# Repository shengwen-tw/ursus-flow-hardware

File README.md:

#Ursus-flow

This is the hardware design of Ursus-flow, a computer vision board provide speed estimation for multi-rotor.

##Specification

**MCU**: STM32F745VETX

**Camera**: MT9v034 (I2C1 and DCMI)

**IMU**: MPU9250 (SPI1)

**Height sensor**: Lidar lite v2 (I2C2)

**USB**: Full Speed USB (USB2.0)

**EEPROM**: AT24C08 (I2C3)

UART2: Data output to flight control board

UART3 and SPI2: alternation

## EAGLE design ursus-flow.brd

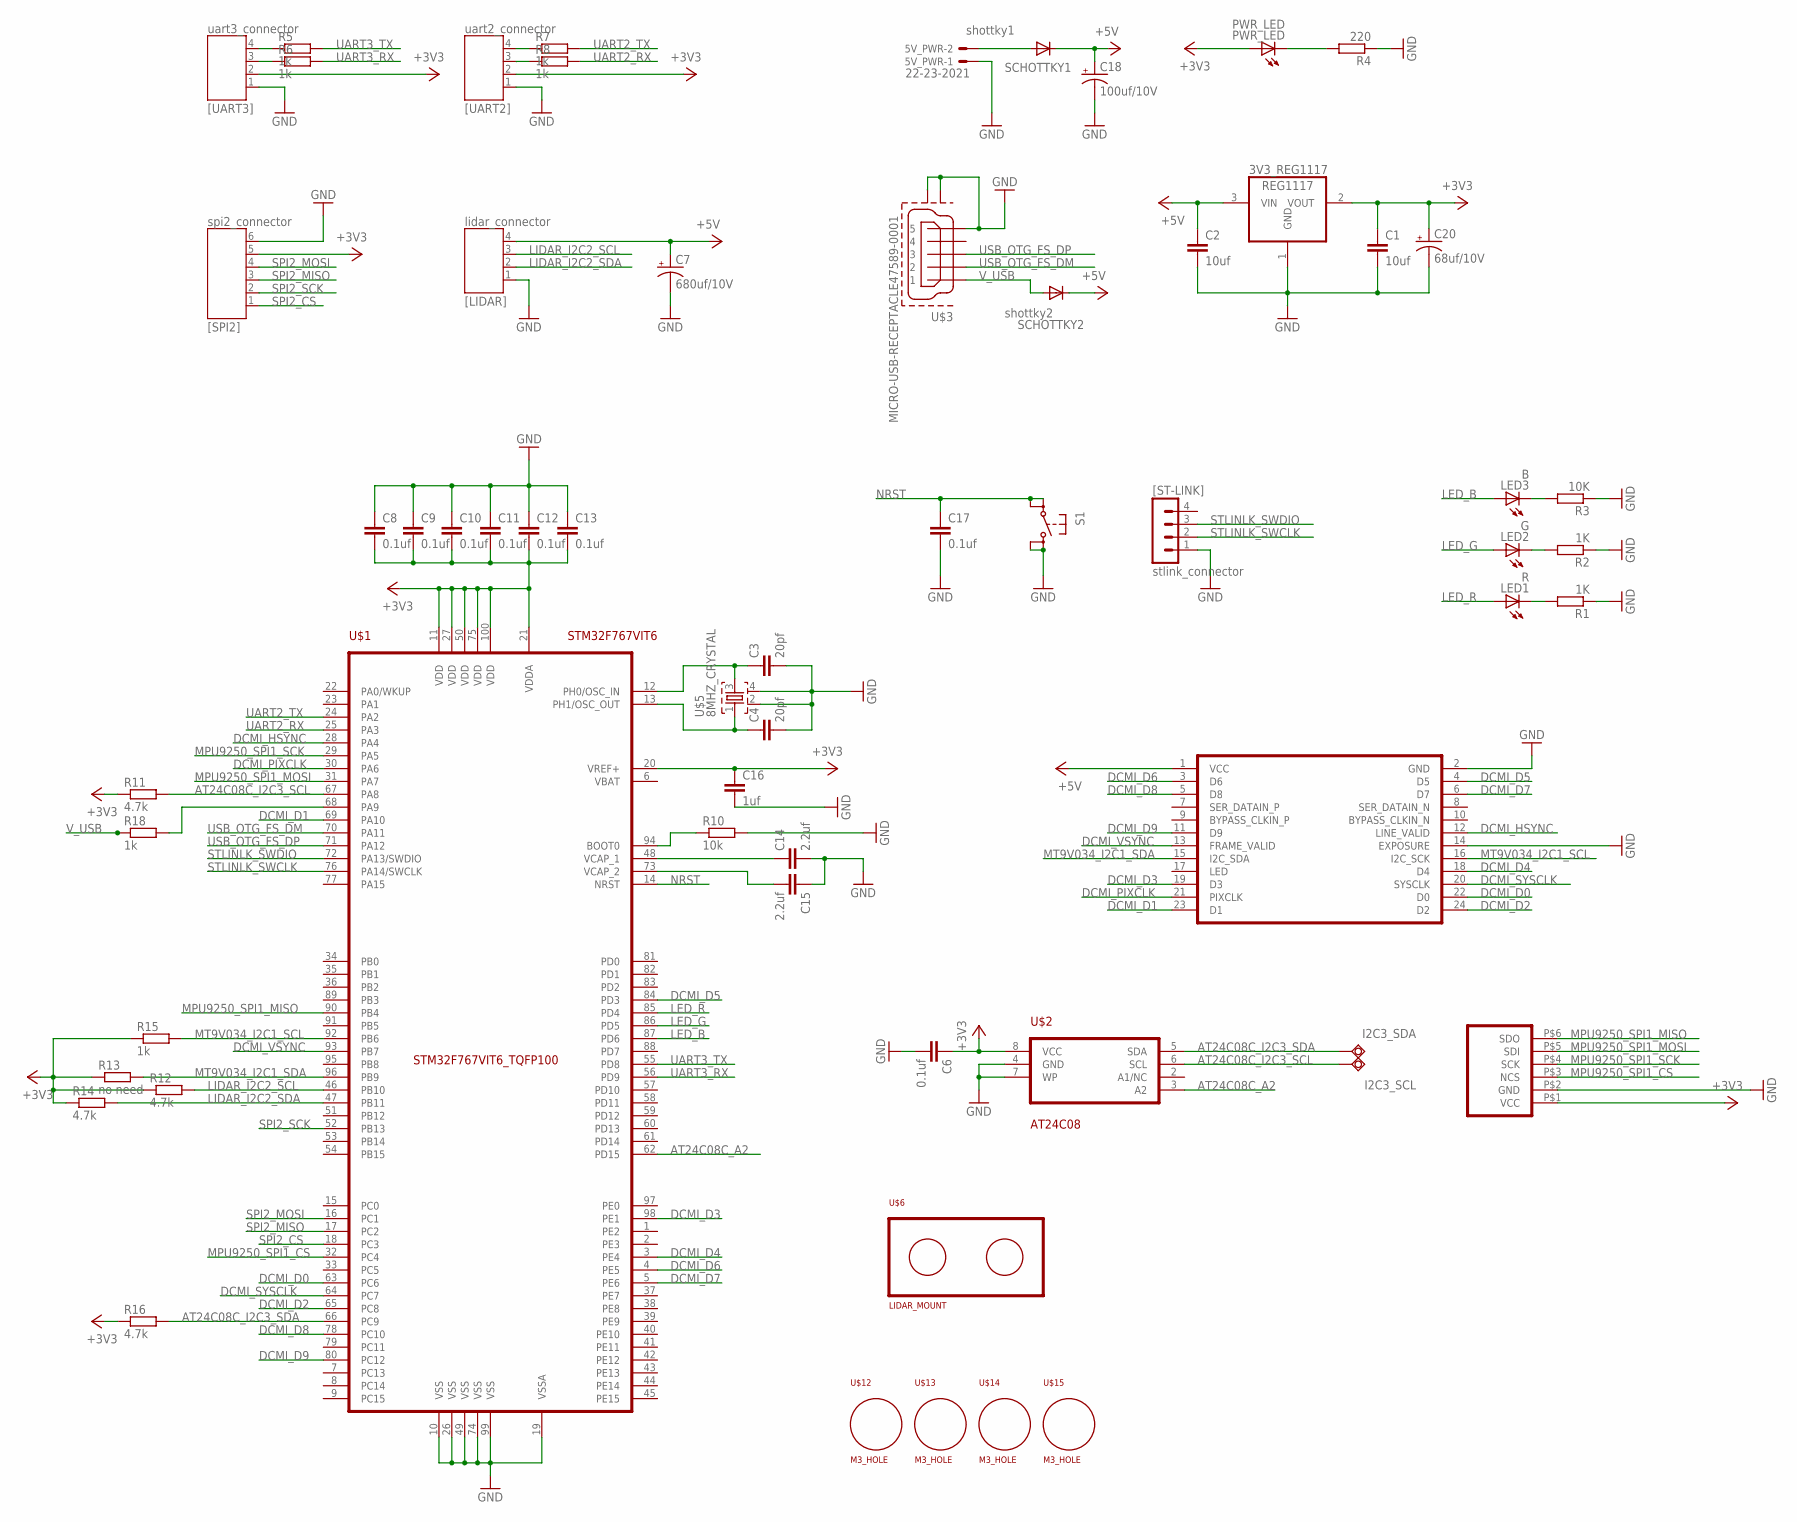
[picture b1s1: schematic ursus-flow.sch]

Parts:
3V3_REG1117: REG1117; SOT223
5V_PWR: 22-23-2021
C1, C2: 10uf; C0805K
C3, C4: 20pf; C0805
C6, C8, C9, C10, C11, C12, C13, C17: 0.1uf; C0805
C7: 680uf/10V; D/7343-31W
C14, C15: 2.2uf; C0805
C16: 1uf; C0805
C18: 100uf/10V; C/6032-28R
C20: 68uf/10V; B/3528-21W
I2C3_SCL, I2C3_SDA: TPSQTP20SQ; TP20SQ
LED1: R; SML0805
LED2: G; SML0805
LED3: B; SML0805
PWR_LED: PWR_LED; SML0805
R1, R2: 1K; R0805W
R3: 10K; R0805W
R4: 220; R0805W
R5, R6, R7, R8: 1k; M0805
R10: 10k; R0805W
R11, R12, R14, R16: 4.7k; R0805W
R13: no need; R0805W
R15, R18: 1k; R0805W
S1: EVQPSL/Q
SCHOTTKY1: shottky1; SOD323-W
SCHOTTKY2: shottky2; SOD323-W
U$1: STM32F767VIT6
U$2: AT24C08; SO8
U$3: MICRO-USB-RECEPTACLE47589-0001; 47589-0001
U$4: MT9V034_MODULE; MA12-2
U$5: 8MHZ_CRYSTAL
U$6: LIDAR_MOUNT
U$11: MPU9250_BREAKOUT
U$12, U$13, U$14, U$15: M3_HOLE
[LIDAR]: lidar_connector; JST-PH4
[SPI2]: spi2_connector; JST-PH6
[ST-LINK]: stlink_connector; MA04-1
[UART2]: uart2_connector; JST-PH4
[UART3]: uart3_connector; JST-PH4

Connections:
+3V3: 3V3_REG1117.2 (VOUT), C1.1, C6.1, C8.2, C9.2, C10.2, C11.2, C12.2, C13.2, C16.1, C20.+, PWR_LED.A, R11.1, R12.1, R13.1, R14.1, R15.1, R16.1, U$1.11 (VDD), U$1.20 (VREF+), U$1.21 (VDDA), U$1.27 (VDD), U$1.50 (VDD), U$1.75 (VDD), U$1.100 (VDD), U$2.8 (VCC), U$11.P$1 (VCC), [SPI2].5, [UART2].2, [UART3].2
+5V: 3V3_REG1117.3 (VIN), C2.1, C7.+, C18.+, SCHOTTKY1.C, SCHOTTKY2.C, U$4.1 (VCC), [LIDAR].4
AT24C08C_A2: U$1.62 (PD15), U$2.3 (A2)
AT24C08C_I2C3_SCL: I2C3_SCL.TP, R11.2, U$1.67 (PA8), U$2.6 (SCL)
AT24C08C_I2C3_SDA: I2C3_SDA.TP, R16.2, U$1.66 (PC9), U$2.5 (SDA)
DCMI_D0: U$1.63 (PC6), U$4.22 (D0)
DCMI_D1: U$1.69 (PA10), U$4.23 (D1)
DCMI_D2: U$1.65 (PC8), U$4.24 (D2)
DCMI_D3: U$1.98 (PE1), U$4.19 (D3)
DCMI_D4: U$1.3 (PE4), U$4.18 (D4)
DCMI_D5: U$1.84 (PD3), U$4.4 (D5)
DCMI_D6: U$1.4 (PE5), U$4.3 (D6)
DCMI_D7: U$1.5 (PE6), U$4.6 (D7)
DCMI_D8: U$1.78 (PC10), U$4.5 (D8)
DCMI_D9: U$1.80 (PC12), U$4.11 (D9)
DCMI_HSYNC: U$1.28 (PA4), U$4.12 (LINE_VALID)
DCMI_PIXCLK: U$1.30 (PA6), U$4.21 (PIXCLK)
DCMI_SYSCLK: U$1.64 (PC7), U$4.20 (SYSCLK)
DCMI_VSYNC: U$1.93 (PB7), U$4.13 (FRAME_VALID)
GND: 3V3_REG1117.1 (GND), 5V_PWR.1, C1.2, C2.2, C3.2, C4.2, C6.2, C7.-, C8.1, C9.1, C10.1, C11.1, C12.1, C13.1, C14.2, C15.1, C16.2, C17.2, C18.-, C20.-, R1.1, R2.1, R3.1, R4.1, R10.2, S1.B (S), S1.B1 (S1), U$1.10 (VSS), U$1.19 (VSSA), U$1.26 (VSS), U$1.49 (VSS), U$1.74 (VSS), U$1.99 (VSS), U$2.4 (GND), U$2.7 (WP), U$3.5, U$3.CASING1 (GND1), U$3.CASING2 (GND2), U$4.2 (GND), U$4.14 (EXPOSURE), U$5.2, U$5.4, U$11.P$2 (GND), [LIDAR].1, [SPI2].6, [ST-LINK].1, [UART2].1, [UART3].1
LED_B: LED3.A, U$1.87 (PD6)
LED_G: LED2.A, U$1.86 (PD5)
LED_R: LED1.A, U$1.85 (PD4)
LIDAR_I2C2_SCL: R12.2, U$1.46 (PB10), [LIDAR].3
LIDAR_I2C2_SDA: R14.2, U$1.47 (PB11), [LIDAR].2
MPU9250_SPI1_CS: U$1.32 (PC4), U$11.P$3 (NCS)
MPU9250_SPI1_MISO: U$1.90 (PB4), U$11.P$6 (SDO)
MPU9250_SPI1_MOSI: U$1.31 (PA7), U$11.P$5 (SDI)
MPU9250_SPI1_SCK: U$1.29 (PA5), U$11.P$4 (SCK)
MT9V034_I2C1_SCL: R15.2, U$1.92 (PB6), U$4.16 (I2C_SCK)
MT9V034_I2C1_SDA: R13.2, U$1.96 (PB9), U$4.15 (I2C_SDA)
unnamed: LED1.C, R1.2
unnamed: LED2.C, R2.2
unnamed: LED3.C, R3.2
unnamed: PWR_LED.C, R4.2
unnamed: 5V_PWR.2, SCHOTTKY1.A
unnamed: C3.1, U$1.12 (PH0/OSC_IN), U$5.3
unnamed: R5.1, [UART3].4
unnamed: R6.1, [UART3].3
unnamed: R7.1, [UART2].4
unnamed: R8.1, [UART2].3
unnamed: C4.1, U$1.13 (PH1/OSC_OUT), U$5.1
unnamed: C14.1, U$1.48 (VCAP_1)
unnamed: C15.2, U$1.73 (VCAP_2)
unnamed: R10.1, U$1.94 (BOOT0)
unnamed: R18.2, U$1.68 (PA9)
NRST: C17.1, S1.A, S1.A1 (P1), U$1.14 (NRST)
SPI2_CS: U$1.18 (PC3), [SPI2].1
SPI2_MISO: U$1.17 (PC2), [SPI2].3
SPI2_MOSI: U$1.16 (PC1), [SPI2].4
SPI2_SCK: U$1.52 (PB13), [SPI2].2
STLINLK_SWCLK: U$1.76 (PA14/SWCLK), [ST-LINK].2
STLINLK_SWDIO: U$1.72 (PA13/SWDIO), [ST-LINK].3
UART2_RX: R8.2, U$1.25 (PA3)
UART2_TX: R7.2, U$1.24 (PA2)
UART3_RX: R6.2, U$1.56 (PD9)
UART3_TX: R5.2, U$1.55 (PD8)
USB_OTG_FS_DM: U$1.70 (PA11), U$3.2
USB_OTG_FS_DP: U$1.71 (PA12), U$3.3
V_USB: R18.1, SCHOTTKY2.A, U$3.1

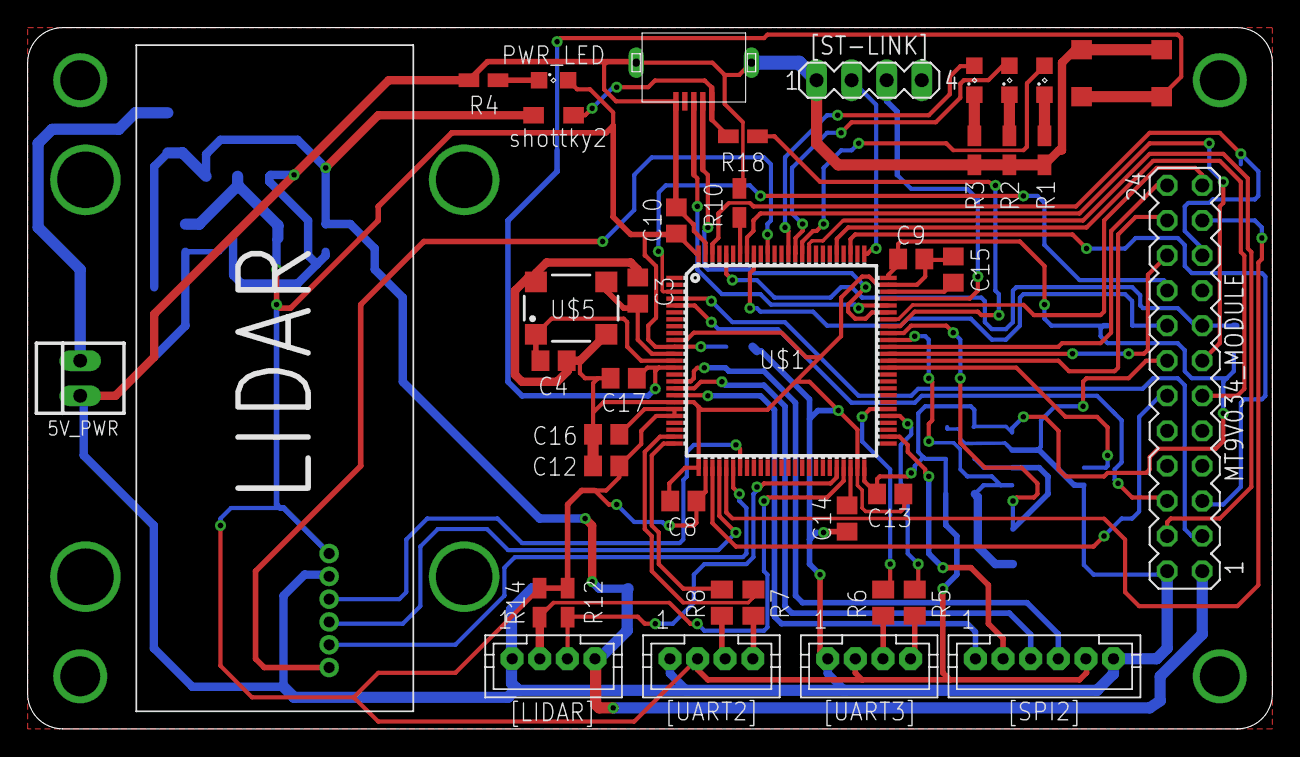
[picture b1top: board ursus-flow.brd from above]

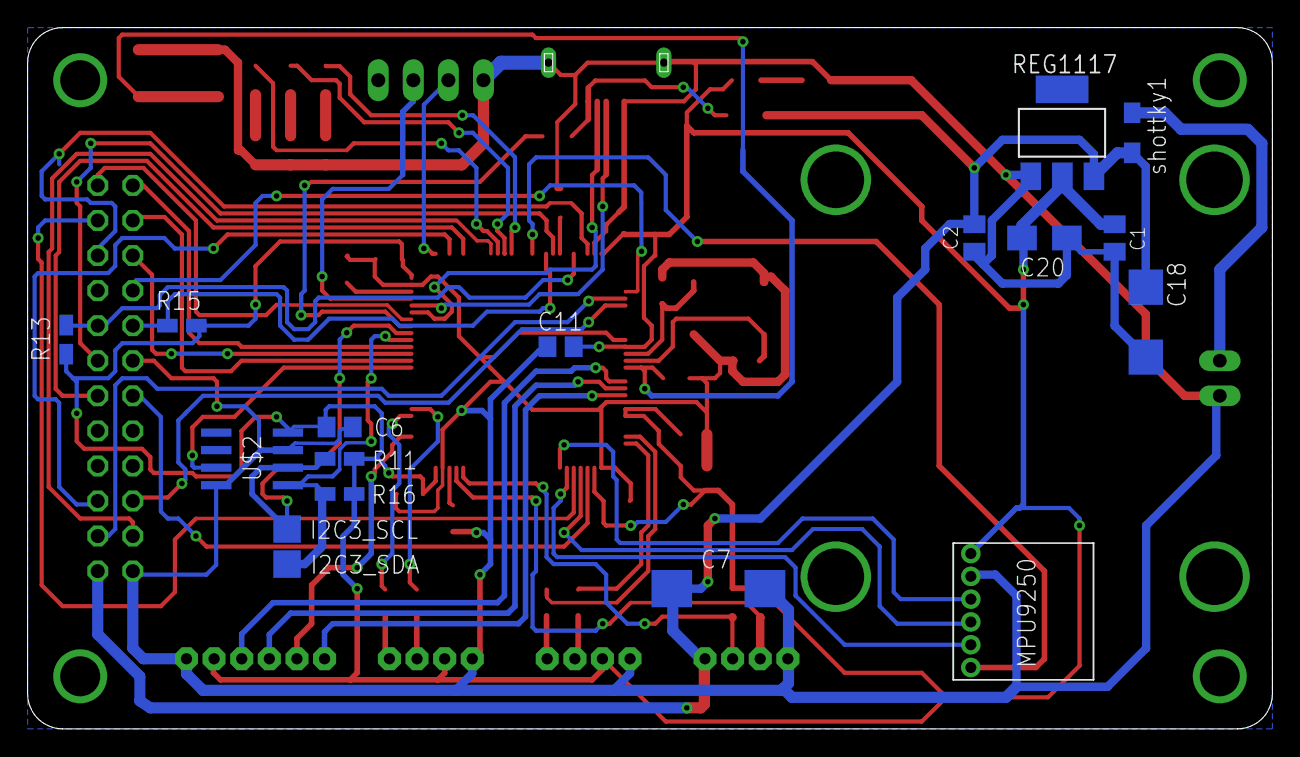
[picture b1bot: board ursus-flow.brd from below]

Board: 2 copper layers, 90.2 x 50.8 mm, 61 parts (17 on the bottom side), 60 nets.

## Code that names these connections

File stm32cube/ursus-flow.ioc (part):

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Mcu.Name=STM32F767V(G-I)Tx
Mcu.Package=LQFP100
Mcu.UserName=STM32F767VITx
PA10.Mode=Slave_10_bits_External_Synchro
PA10.Signal=DCMI_D1
PA11.Mode=Device_Only
PA11.Signal=USB_OTG_FS_DM
PA12.Mode=Device_Only
PA12.Signal=USB_OTG_FS_DP
PA13.GPIOParameters=GPIO_Label
PA13.GPIO_Label=STLINK-SWDIO
PA13.Mode=Serial_Wire
PA13.Signal=SYS_JTMS-SWDIO
PA14.GPIOParameters=GPIO_Label
PA14.GPIO_Label=STLINK-SWCLK
PA14.Mode=Serial_Wire
PA14.Signal=SYS_JTCK-SWCLK
PA2.Mode=Asynchronous
PA2.Signal=USART2_TX
PA3.Mode=Asynchronous
PA3.Signal=USART2_RX
PA4.Mode=Slave_10_bits_External_Synchro
PA4.Signal=DCMI_HSYNC
PA5.GPIOParameters=GPIO_Label
PA5.GPIO_Label=MPU9250_SPI1_SCK
PA5.Mode=Full_Duplex_Master
PA5.Signal=SPI1_SCK
PA6.Mode=Slave_10_bits_External_Synchro
PA6.Signal=DCMI_PIXCLK
PA7.GPIOParameters=GPIO_Label
PA7.GPIO_Label=MPU9250_SPI1_MOSI
PA7.Mode=Full_Duplex_Master
PA7.Signal=SPI1_MOSI
PA8.GPIOParameters=GPIO_Label
PA8.GPIO_Label=AT24C08C_I2C3_SCL
PA8.Mode=I2C
PA8.Signal=I2C3_SCL
PA9.Mode=Activate_VBUS
PA9.Signal=USB_OTG_FS_VBUS
PB10.GPIOParameters=GPIO_Label
PB10.GPIO_Label=LIDAR_I2C2_SCL
PB10.Mode=I2C
PB10.Signal=I2C2_SCL
PB11.GPIOParameters=GPIO_Label
PB11.GPIO_Label=LIDAR_I2C2_SDA
PB11.Mode=I2C
PB11.Signal=I2C2_SDA
PB13.Mode=Full_Duplex_Master
PB13.Signal=SPI2_SCK
PB4.GPIOParameters=GPIO_Label
PB4.GPIO_Label=MPU9250_SPI1_MISO
PB4.Mode=Full_Duplex_Master
PB4.Signal=SPI1_MISO
PB6.GPIOParameters=GPIO_Label
PB6.GPIO_Label=MT9V034_I2C1_SCL
PB6.Mode=I2C
PB6.Signal=I2C1_SCL
PB7.Mode=Slave_10_bits_External_Synchro
PB7.Signal=DCMI_VSYNC
PB9.GPIOParameters=GPIO_Label
PB9.GPIO_Label=MT9V034_I2C1_SDA
PB9.Mode=I2C
PB9.Signal=I2C1_SDA
PC1.Mode=Full_Duplex_Master
PC1.Signal=SPI2_MOSI
PC10.Mode=Slave_10_bits_External_Synchro
PC10.Signal=DCMI_D8
PC12.Mode=Slave_10_bits_External_Synchro
PC12.Signal=DCMI_D9
PC2.Mode=Full_Duplex_Master
PC2.Signal=SPI2_MISO
PC3.GPIOParameters=GPIO_Label
PC3.GPIO_Label=SPI2_CS
PC3.Signal=GPIO_Output
PC4.GPIOParameters=GPIO_Label
PC4.GPIO_Label=MPU9250_SPI1_CS
PC4.Signal=GPIO_Output
PC6.Mode=Slave_10_bits_External_Synchro
PC6.Signal=DCMI_D0
PC7.GPIOParameters=GPIO_Label
PC7.GPIO_Label=DCMI_SYSCLK
PC7.Signal=S_TIM8_CH2
PC8.Mode=Slave_10_bits_External_Synchro
PC8.Signal=DCMI_D2
PC9.GPIOParameters=GPIO_Label
PC9.GPIO_Label=AT24C08C_I2C3_SDA
PC9.Mode=I2C
PC9.Signal=I2C3_SDA
PD3.Mode=Slave_10_bits_External_Synchro
PD3.Signal=DCMI_D5
PD4.GPIOParameters=GPIO_Label
PD4.GPIO_Label=LED_R
PD4.Signal=GPIO_Output
PD5.GPIOParameters=GPIO_Label
PD5.GPIO_Label=LED_G
PD5.Signal=GPIO_Output
PD6.GPIOParameters=GPIO_Label
PD6.GPIO_Label=LED_B
PD6.Signal=GPIO_Output
PD8.Mode=Asynchronous
PD8.Signal=USART3_TX
PD9.Mode=Asynchronous
PD9.Signal=USART3_RX
PE1.Mode=Slave_10_bits_External_Synchro
PE1.Signal=DCMI_D3
PE4.Mode=Slave_10_bits_External_Synchro
PE4.Signal=DCMI_D4
PE5.Mode=Slave_10_bits_External_Synchro
PE5.Signal=DCMI_D6
PE6.Mode=Slave_10_bits_External_Synchro
PE6.Signal=DCMI_D7
PH0/OSC_IN.Mode=HSE-External-Oscillator
PH0/OSC_IN.Signal=RCC_OSC_IN
PH1/OSC_OUT.Mode=HSE-External-Oscillator
PH1/OSC_OUT.Signal=RCC_OSC_OUT
RCC.HSE_VALUE=8000000
RCC.SYSCLKFreq_VALUE=32000000
RCC.SYSCLKSource=RCC_SYSCLKSOURCE_PLLCLK

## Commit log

2016-12-21 Create new eagle project
2016-12-21 Add STM32CubeMX project
2016-12-23 Save circuit 2016/12/24
2016-12-24 Save 2016/12/24
2016-12-24 Save 2016/12/25 Happy Christmas
2016-12-25 Fix diode and connector
2016-12-30 2016/12/30 Good bye 2016
2017-01-04 Add MPU9250 breakout board
2017-01-27 Update MT9V034 and MPU9250
2017-01-27 Remove redundent backup files
2017-01-27 Arrange components
2017-01-27 Remove wrong footprint of MPU9250
2017-01-28 Start doing PCB layout
2017-01-28 Fix cube label
2017-01-28 Keep routing
2017-01-28 Layout is almost done
2017-01-28 Connect more traces
2017-01-30 Finish PCB layout
2017-01-30 Add picture
2017-01-30 Fix small errors
2017-01-30 Adjust labels
2017-02-01 Add IMU logo
2017-02-01 Adjust MPU9250 drill size
2017-02-19 Do circuit final check
2017-02-19 Adjust logo
2017-02-20 Remove trash dove
2017-02-22 Save project setting
2017-03-19 Update component value
2017-03-19 Update project manage file
2017-03-28 Update pull up resistors for mt9v034

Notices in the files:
parts and their libraries:
switch-panasonic: Copyright (C) 2010, Bob Starr
usb_mirco_b: (C) 2014 Tomasz Boleslaw CEDRO, cederom@tlen.pl, http://www.tomek.cedro.info.
